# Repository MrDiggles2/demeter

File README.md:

# Demeter

Low power, wireless plant moisture sensors.

|Module|Description|
|--|--|
|`sensor`|Sensor built on ESP12E. Publishes data to MQTT. Low power usage, can last months on a single battery charge|
|`aggregator`|Node server that collected sensor data and exposes it via API|
|`display`|ESP12E and eInk module. Pulls data from server and displays data at a slow cadence|

<table>
  <tr>
    <td></td>
    <td></td>
  </tr>
</table>

### TODOs

* Figure out how to interpret raw values from sensors for display
* Hook up pager duty

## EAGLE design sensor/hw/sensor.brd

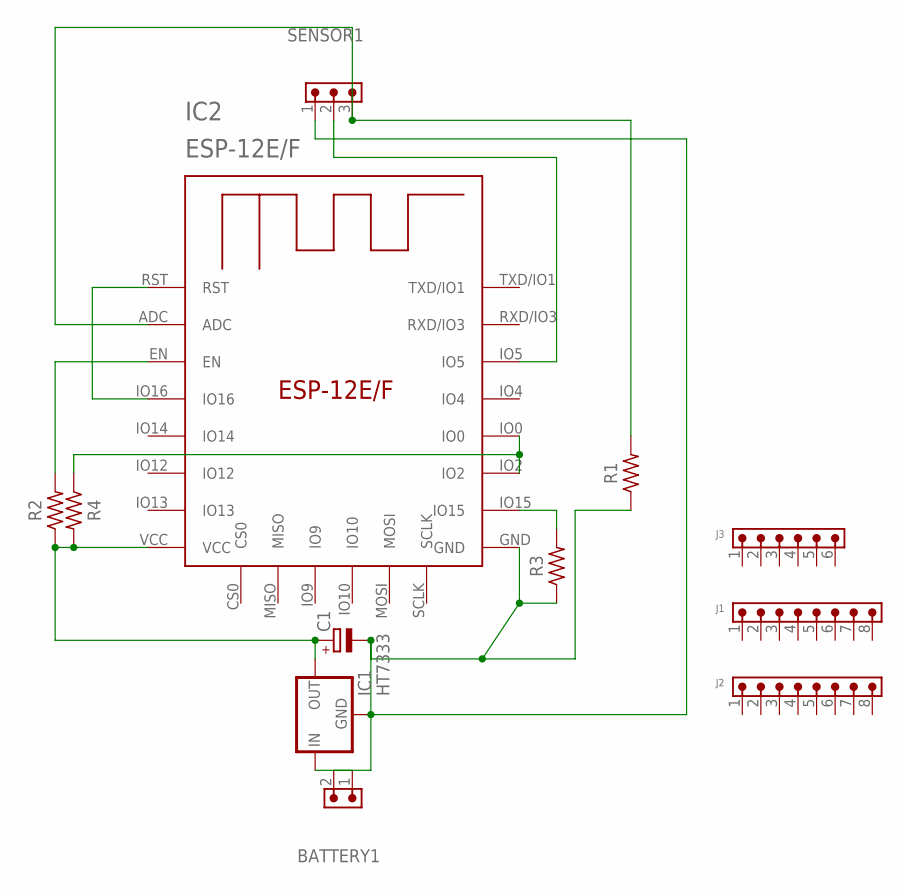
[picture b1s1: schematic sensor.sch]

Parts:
BATTERY1: 6130XX11121_61300211121; 61300211121
C1: CPOL-EUE2-5; E2-5
IC1: HT7333; SOT-89
IC2: ESP-12E/F; ESP-12E
J1, J2: 6200XX11121_62000811121; 62000811121
J3: 6200XX11121_62000611121; 62000611121
R1, R2, R3, R4: R-US_AXIAL-7.2MM-PITCH; RESAD724W46L381D178B
SENSOR1: 6130XX11121_61300311121; 61300311121

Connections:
unnamed: IC2.IO5, SENSOR1.2
unnamed: IC2.IO0, IC2.IO2, R4.1
unnamed: IC2.ADC, R1.2, SENSOR1.3
unnamed: BATTERY1.1, IC1.3 (IN), IC1.4 (IN)
unnamed: IC2.EN, R2.2
unnamed: IC2.IO16, IC2.RST
unnamed: IC2.IO15, R3.2
unnamed: BATTERY1.2, C1.-, IC1.2 (GND), IC2.GND, R1.1, R3.1, SENSOR1.1
unnamed: C1.+, IC1.1 (OUT), IC2.VCC, R2.1, R4.2

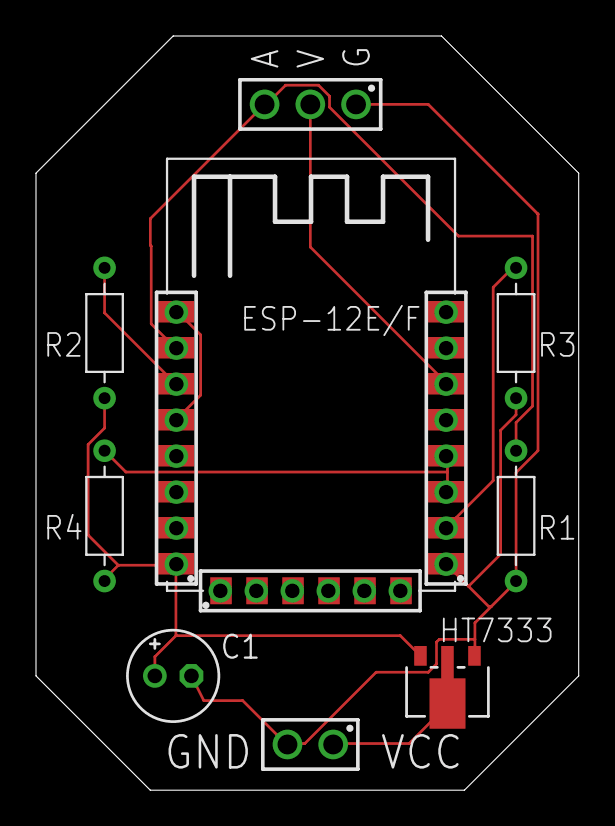
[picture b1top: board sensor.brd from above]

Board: 2 copper layers, 30.1 x 41.9 mm, 12 parts (0 on the bottom side), 9 nets.

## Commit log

2020-11-07 adds dynamic max min
2020-11-07 more minor changes
2020-11-07 adds code to preserve max and min values between resets
2020-11-07 moves publishing to separate function. adds hard reset option for bounds
2020-11-07 minor debug changes
2020-11-08 minor changes
2020-11-09 initial commit of server
2020-11-27 clean up on backend
2020-11-27 moves stuff around
2021-02-24 simplifies set up
2021-02-24 rearranges some files; fixes dependencies
2021-02-24 fix dependencies
2021-02-24 depe
2021-02-24 adds aggregator systemd file
2021-02-24 adds systemd file
2021-02-24 adds install script
2021-02-24 adds status to install
2021-02-24 renames install to install-service for clarity
2021-02-24 adds no pager option to install service script
2021-02-24 final touch for sensor
2021-02-24 reverts back to using nodemon
2021-02-24 fixes query
2021-02-24 updates endpoint to use count instead of date range
2021-03-04 fixes deepsleep; adds timestamp column
2021-03-05 adds view for chart
2021-03-05 integrates with current data
2021-03-05 fixes node path
2021-03-05 adds cors support
2021-03-05 makes api call relative
2021-03-25 sensor updates
2021-03-25 forwards count parameter to rasp
2021-03-25 adds support for name filtering
2021-06-08 updates to power sensor with gpio instead of vcc
2021-06-08 fixes comment
2021-07-13 adds EAGLE files
2021-10-30 adds support for status updates
2021-10-30 bumps sleep cycles to 6 hours
2021-10-30 puts in a sample value since i'm too lazy to figure out the caluclation right now
2021-10-31 removes raw data from status api
2021-10-31 randomizes value for testing
2021-11-02 adds sensor notes; adds initial display code
2021-11-02 adds readme
2021-11-02 intial commit of regression test
2021-11-20 stash
2021-11-21 incremtnal commit;
2021-11-25 finishes implementation of db service + tests
2021-11-25 installs typescript; converts db service
2021-11-25 converts main to typescrip
2021-11-25 fixes readings endpoint
2021-11-26 finishes up ts migration
2021-11-26 implements isAlive
2021-11-26 fixes webpack build
2021-11-28 installs regression
2021-12-08 adds package-lock
2021-12-08 fixes readings api
2021-12-08 typo
2021-12-11 adds a compact status
2021-12-16 adds a limit to status
2021-12-16 shrinks memory usage of display.ino
2021-12-16 adds migration helpers
2021-12-16 removes unused const
2021-12-16 ignores all sqlite files
2021-12-16 minor adjustments to display
2022-02-21 doc update

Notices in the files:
parts and their libraries:
Wurth_Connectors_WR-PHD: Copyright: Würth Elektronik
